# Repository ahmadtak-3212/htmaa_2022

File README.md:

# htmaa_2022: MIT How to Make (Almost) Anything, fall 2022

My weekly assignments from MIT's **How to Make (Almost) Anything** (MAS.863, Sept 7 – Dec 14, 2022), with one folder per assignment. Each folder has its design files and a README explaining how to rebuild it. The full write-ups, with photos and videos, are in [`docs/writeups/`](docs/writeups).

My final project was **Oliya**, a full-size electric ATV built with Raiphy. It has its own repo: **[oliya_project](https://github.com/ahmadtak-3212/oliya_project)**. Weeks 5 and 7–10 (the ATV's dashboard display and audio system), week 8 (the ATV emblem) and week 14 (the welded hood) fed straight into it, so their design files live there.

| Week 3 programmer | Week 6 chest | Week 11 CAN boards |
|---|---|---|
|  |  |  |

## Weeks

| Week | Assignment | What I made | Files | Write-up |
|---|---|---|---|---|
| 1 | 3D design | Oliya ATV concept CAD | [oliya_project](https://github.com/ahmadtak-3212/oliya_project) | [week01](docs/writeups/week01_3d_design.md) |
| 2 | Laser and vinyl cutting | Parametric living-hinge box; vinyl-cut calligraphy | [`week02_living_hinge_box`](week02_living_hinge_box) | [week02](docs/writeups/week02_laser_and_vinyl_cutting.md) |
| 3 | Electronics production | Milled SAMD11C CMSIS-DAP programmer | [`week03_d11c_programmer`](week03_d11c_programmer) | [week03](docs/writeups/week03_electronics_production.md) |
| 4 | 3D printing and scanning | Topology-optimized pencil cup | [`week04_topology_cup`](week04_topology_cup) | [week04](docs/writeups/week04_3d_printing.md) |
| 5 | Electronics design | ATtiny1614 + OLED board (ATV dashboard display) | [`week05_oled_display_board`](week05_oled_display_board) | [week05](docs/writeups/week05_electronics_design.md) |
| 6 | Computer-controlled machining | Parametric CNC-routed plywood chest | [`week06_plywood_chest`](week06_plywood_chest) | [week06](docs/writeups/week06_computer_controlled_machining.md) |
| 7 | Embedded programming | Spectrum analyzer / audio amplifier | [oliya_project](https://github.com/ahmadtak-3212/oliya_project) | [week07](docs/writeups/week07_embedded_programming.md) |
| 8 | Molding and casting | Oliya emblem | [oliya_project](https://github.com/ahmadtak-3212/oliya_project) | [week08](docs/writeups/week08_molding_and_casting.md) |
| 9 | Input devices | Audio mixer and waveform display input | [oliya_project](https://github.com/ahmadtak-3212/oliya_project) | [week09](docs/writeups/week09_input_devices.md) |
| 10 | Output devices | Bridged LM386 speaker amplifier | [oliya_project](https://github.com/ahmadtak-3212/oliya_project) | [week10](docs/writeups/week10_output_devices.md) |
| 11 | Networking | SAMD21 + MCP2515 CAN sender and receiver | [`week11_12_can_bus_link`](week11_12_can_bus_link), [`week11_can_bus_board_v0`](week11_can_bus_board_v0) | [week11](docs/writeups/week11_networking.md) |
| 12 | Interface programming | Kivy CAN logger app | [`week11_12_can_bus_link`](week11_12_can_bus_link) | [week12](docs/writeups/week12_interface_programming.md) |
| 13 | Machine building | Group drawing machine | [HTM_Drawing_Bot](https://github.com/ahmadtak-3212/HTM_Drawing_Bot) (team repo) | [week13](docs/writeups/week13_machine_building.md) |
| 14 | Wildcard | Sheet metal and welding (ATV hood) | [oliya_project](https://github.com/ahmadtak-3212/oliya_project) | [week14](docs/writeups/week14_wildcard_welding.md) |

**Week 13 was a group project** and lives in the team's own repo, [HTM_Drawing_Bot](https://github.com/ahmadtak-3212/HTM_Drawing_Bot). My parts were:
- organizing the group and setting up the team repo;
- machining the aluminum-extrusion frame (cutting 2060 extrusion to size and machining a 2060 down to a 2020 for the x-axis);
- sourcing the base and printing corner brackets;
- designing the limit-switch PCB.

## Tools used

| Kind | Tools |
|---|---|
| CAD | SolidWorks (including Simulation / topology study), Fusion 360 (CAM) |
| Electronics | KiCad 6; boards milled on a Bantam desktop mill |
| Firmware | Arduino IDE with megaTinyCore (ATtiny1614) and a SAMD core (SAMD11/SAMD21); `edbg` for SWD flashing |
| Software | Python 3.9 + Kivy 2.1 + pyserial |
| Fabrication | Laser cutter, vinyl cutter, Ultimaker S5, shop CNC router, water jet, MIG welder |

## Layout

```
htmaa_2022/
├── docs/
│   ├── writeups/        one Markdown write-up per week
│   └── images/weekNN/   photos, videos, downloads referenced by the write-ups
│       └── renders/     PCB renders generated from the Gerbers
└── weekNN_<name>/       design files for that week (each has its own README)
```

The write-ups were converted from my original class documentation pages. See [docs/STRUCTURE.md](docs/STRUCTURE.md) for the folder conventions.

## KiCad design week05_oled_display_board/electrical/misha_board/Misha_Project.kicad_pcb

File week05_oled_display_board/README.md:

# Week 5: ATtiny1614 OLED display board

An "echo hello-world" board with an **ATtiny1614**, a button, an LED, and an I²C header for a **0.96" SSD1306 OLED**. It was designed as the first version of the audio display for the dashboard of the [Oliya electric ATV](https://github.com/ahmadtak-3212/oliya_project).

| Result | Board render |
|---|---|
|  |  |

Full write-up: [week05_electronics_design.md](../docs/writeups/week05_electronics_design.md)

## Files

| Path | What |
|---|---|
| `electrical/misha_board/Misha_Project.kicad_pro` | KiCad 6 project, 53.8 × 40 mm, milled single-sided with two 0 Ω jumpers and a ground pour |
| `electrical/misha_board/gbr/` | Milling Gerbers (`F_Cu`, `Edge_Cuts`, drill) |
| `electrical/misha_board/ATTINY1614/` | Symbol and footprint for the ATtiny1614-SSF |
| `firmware/firmware.ino` | Display test sketch |

**Connectors:** `J1` I²C (to the OLED), `J2` UPDI (programming), `J3` FTDI serial, and `SW1` button on **PA4**.

## Rebuild

1. Mill with a 1/64" end mill for traces, a 1/32" end mill for the outline and a 1/8" end mill for clearing. The design rules are 16 mil trace and clearance. Sand the board after milling, because a leftover copper sliver caused a short.
2. **Arduino IDE setup:** add `http://drazzy.com/package_drazzy.com_index.json` to the Boards Manager URLs and install Spence Konde's core for the ATtiny 0/1-series (**megaTinyCore**). Select ATtiny1614, with programmer **"Serial UPDI – SLOW"**, and program through a USB-serial adapter on the UPDI header.
3. First flash the class echo sketch (`hello.t1614.echo.ino`) and check it over the FTDI header.
4. Install **Adafruit GFX** and **Adafruit SSD1306**, then upload `firmware/firmware.ino`. The display (128 × 32 at I²C address 0x3C) turns black while the button is held and white otherwise.

## Results

Both the echo test and the display sketch worked. This board was the starting point for the display and audio boards that ended up on Oliya.

_Formerly `misha_project`. Part of [htmaa_2022](../README.md), MIT How to Make (Almost) Anything, fall 2022._

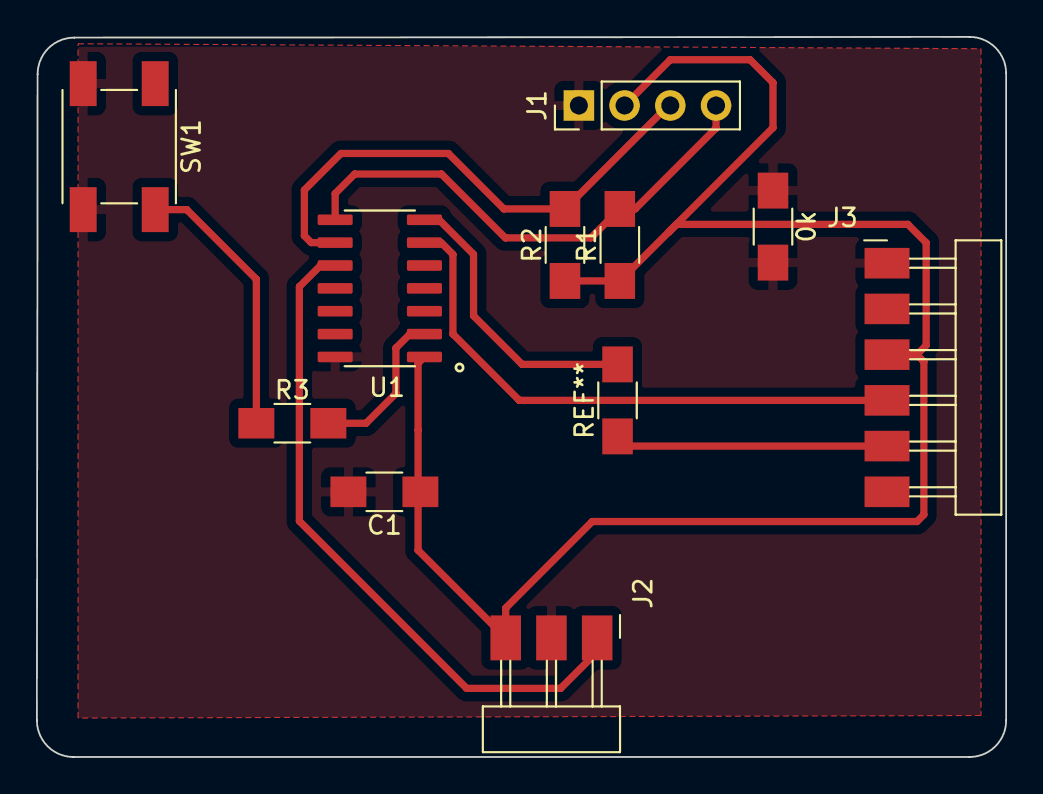
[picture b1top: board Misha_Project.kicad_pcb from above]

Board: 2 copper layers, 53.8 x 40.0 mm, 10 parts (0 on the bottom side), 8 nets.

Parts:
0k: R_1206
C1: 1uF; C_1206
J1: I2C; PinHeader_1x04_P2.54mm_Vertical
J2: UPDI; PinHeader_1x03_P2.54mm_Horizontal_SMD
J3: FTDI; PinHeader_1x06_P2.54mm_Horizontal_SMD
R1, R2: 5K; R_1206
R3: 0K; R_1206
SW1: Button; Button_Omron_B3SN_6.0x6.0mm
U1: ATTINY1614-SSF; SOIC127P600X175-14N

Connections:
Button: R3.1, R3.2, SW1.1, U1.2 (PA4)
GND: 0k.1, 0k.2, C1.2, J1.1, J2.2, J3.1, SW1.2, U1.14 (GND)
RX: J3.5, U1.7 (PB2/OSC2)
SCL: J1.3, R2.2, U1.9 (PB0)
SDA: J1.4, R1.2, U1.8 (PB1)
TX: J3.4, U1.6 (PB3/OSC1)
UDPI: J2.1, U1.10 (PA0/~RESET/UDPI)
VCC: C1.1, J1.2, J2.3, J3.3, R1.1, R2.1, U1.1 (VDD)

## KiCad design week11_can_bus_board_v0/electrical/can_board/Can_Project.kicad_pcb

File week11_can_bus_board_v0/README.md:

# Week 11: SAMD21 CAN board, early version

The first layout of the week 11 CAN board: an ATSAMD21E18A, AP1117-5.0 and NCP1117-3.3 regulators, a power switch, a 10-pin SWD header, and a 7-pin socket for an MCP2515 module, on a 40 × 45 mm board. It was superseded by the sender and receiver pair in [`../week11_12_can_bus_link`](../week11_12_can_bus_link), which is the version that was built and tested.

Full write-up: [week11_networking.md](../docs/writeups/week11_networking.md)

## Files

| Path | What |
|---|---|
| `electrical/can_board/Can_Project.kicad_pro` | KiCad 6 project (schematic + PCB). No Gerbers were exported. |
| `electrical/can_board/samd21.pretty/` | SAMD21E (TQFP-32) footprint |

_Formerly `can_project`. Part of [htmaa_2022](../README.md), MIT How to Make (Almost) Anything, fall 2022._

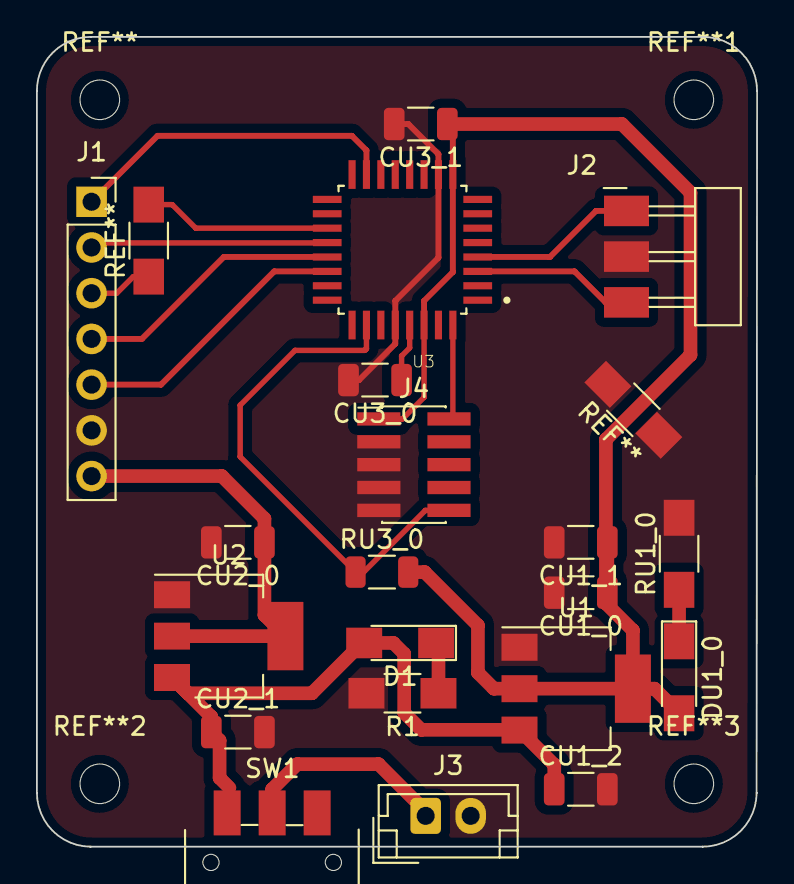
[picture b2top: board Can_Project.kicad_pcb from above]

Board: 2 copper layers, 40.0 x 45.0 mm, 20 parts (0 on the bottom side), 18 nets.

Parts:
CU1_0: 1uF; C_1206_3216Metric
CU1_1, CU1_2, CU2_0, CU2_1, CU3_0, CU3_1: 10uF; C_1206_3216Metric
D1: LED_1206
DU1_0: LED_1206
J1: Conn_01x07_Female; PinSocket_1x07_P2.54mm_Vertical
J2: Conn_PinHeader_1x03_P2.54mm_Horizontal_SMD; PinHeader_1x03_P2.54mm_Horizontal_SMD
J3: Conn_01x02_Female; JST_EH_B2B-EH-A_1x02_P2.50mm_Vertical
J4: CONN_05X2_ARM_DEBUG; PinHeader_2x05_P1.27mm_Vertical_SMD
R1: 10K; R_1206
RU1_0: 5K; R_1206
RU3_0: 10k; R_1206_3216Metric
SW1: SWITCH_JS102011JCQN; Switch_SPDT_CnK_JS102011JCQN_9x3.6mm_P2.5mm
U1: NCP1117-3.3_SOT223; SOT-223-3_TabPin2
U2: AP1117-50; SOT-223-3_TabPin2
U3: ATSAMD21E18A-AF; QFP80P900X900X120-32N

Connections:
+3.3V: CU1_0.1, CU1_1.1, CU3_1.1, DU1_0.2 (A), J4.1 (VCC), RU3_0.2, U1.2 (VO), U3.9 (VDDANA), U3.30 (VDDIN)
+5V: CU2_0.1, J1.7, U2.2 (VO)
+9V: CU1_2.1, CU2_1.1, D1.2 (A), SW1.1 (A), U1.3 (VI), U2.3 (VI)
/A2: J2.3, U3.3 (PA02)
/A3: J2.1, U3.4 (PA03)
/CAN_INT: J1.1, U3.15 (PA14)
/MISO: J1.4, U3.21 (PA22)
/MOSI: J1.3, U3.19 (PA18)
/NRST: J4.10 (NRESET), RU3_0.1, U3.26 (~RESET)
/SCK: J1.2, U3.20 (PA19)
/SS_CAN: J1.5, U3.22 (PA23)
/SWCLK: J4.4 (SWDCLK/TCK), U3.31 (PA30)
/SWDIO: J4.2 (SWDIO/TMS), U3.32 (PA31)
/VDDCORE: CU3_0.1, U3.29 (VDDCORE)
GND: CU1_0.2, CU1_1.2, CU1_2.2, CU2_0.2, CU2_1.2, CU3_0.2, CU3_1.2, J1.6, J2.2, J3.2, J4.3 (GND@3), J4.5 (GND@5), J4.7 (GND@7), J4.9 (GND@9), R1.2, RU1_0.2, U1.1 (GND), U2.1 (GND), U3.10 (GND), U3.28 (GND)
unnamed: D1.1 (K), R1.1
unnamed: J3.1, SW1.2 (B)
unnamed: DU1_0.1 (K), RU1_0.1
